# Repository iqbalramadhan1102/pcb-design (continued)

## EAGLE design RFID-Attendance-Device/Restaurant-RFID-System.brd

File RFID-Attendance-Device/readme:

RFID Device to monitor the employee attendance.

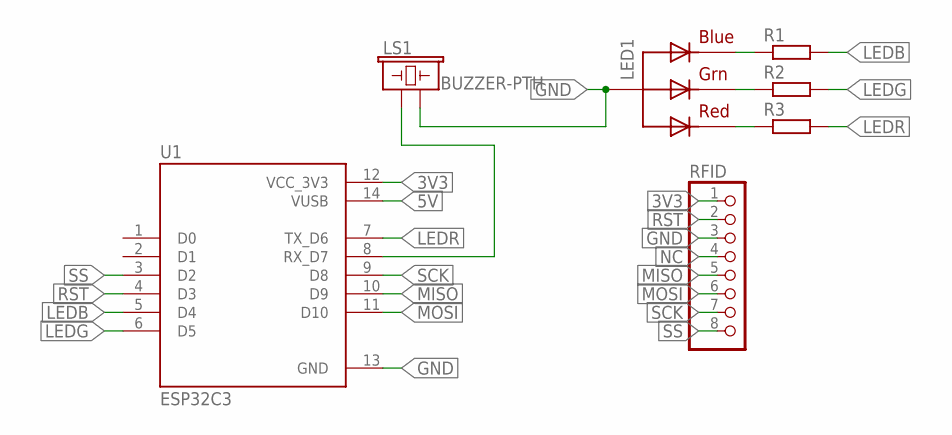
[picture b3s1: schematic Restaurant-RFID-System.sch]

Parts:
LED1: RGBLED_CA-5MM; LED5MMRGB
LS1: BUZZER-PTH; BUZZER-12MM
R1, R2, R3: R-EU_R0805; R0805
RFID: PINHD-1X8; 1X08
U1: ESP32C3; MODULE_113991054

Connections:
3V3: RFID.1, U1.12 (VCC_3V3)
5V: U1.14 (VUSB)
GND: LED1.2 (VCC), LS1.- (2), RFID.3, U1.13 (GND)
LEDB: R1.2, U1.5 (D4)
LEDG: R2.2, U1.6 (D5)
LEDR: R3.2, U1.7 (TX_D6)
MISO: RFID.5, U1.10 (D9)
MOSI: RFID.6, U1.11 (D10)
unnamed: LED1.4 (BLUE), R1.1
unnamed: LED1.3 (GREEN), R2.1
unnamed: LED1.1 (RED), R3.1
unnamed: LS1.+ (1), U1.8 (RX_D7)
NC: RFID.4
RST: RFID.2, U1.4 (D3)
SCK: RFID.7, U1.9 (D8)
SS: RFID.8, U1.3 (D2)

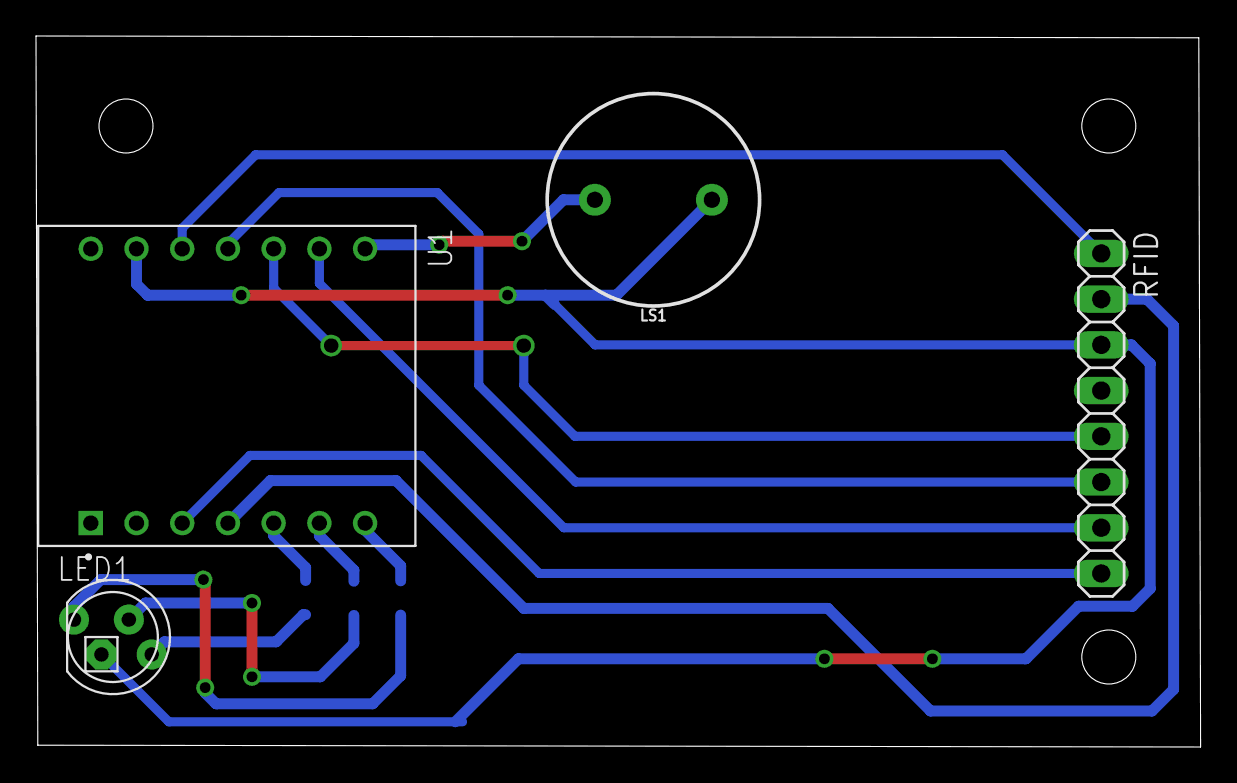
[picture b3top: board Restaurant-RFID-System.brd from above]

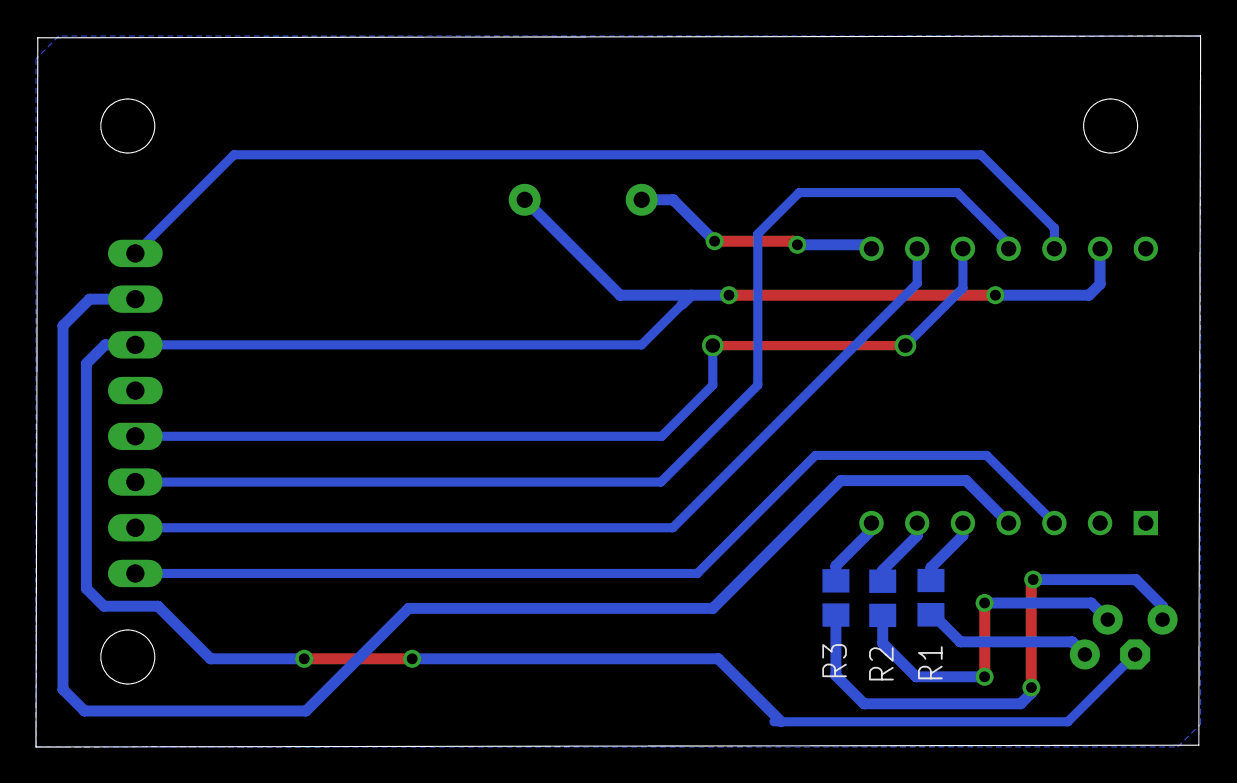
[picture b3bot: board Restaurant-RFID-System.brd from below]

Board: 2 copper layers, 64.7 x 39.5 mm, 7 parts (3 on the bottom side), 14 nets.
